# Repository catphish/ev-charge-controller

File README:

Charge Controller
=================

This controller has connectivity for CAN and EVSE as well as 4 x 12V digital inputs and 4 x low side switches.

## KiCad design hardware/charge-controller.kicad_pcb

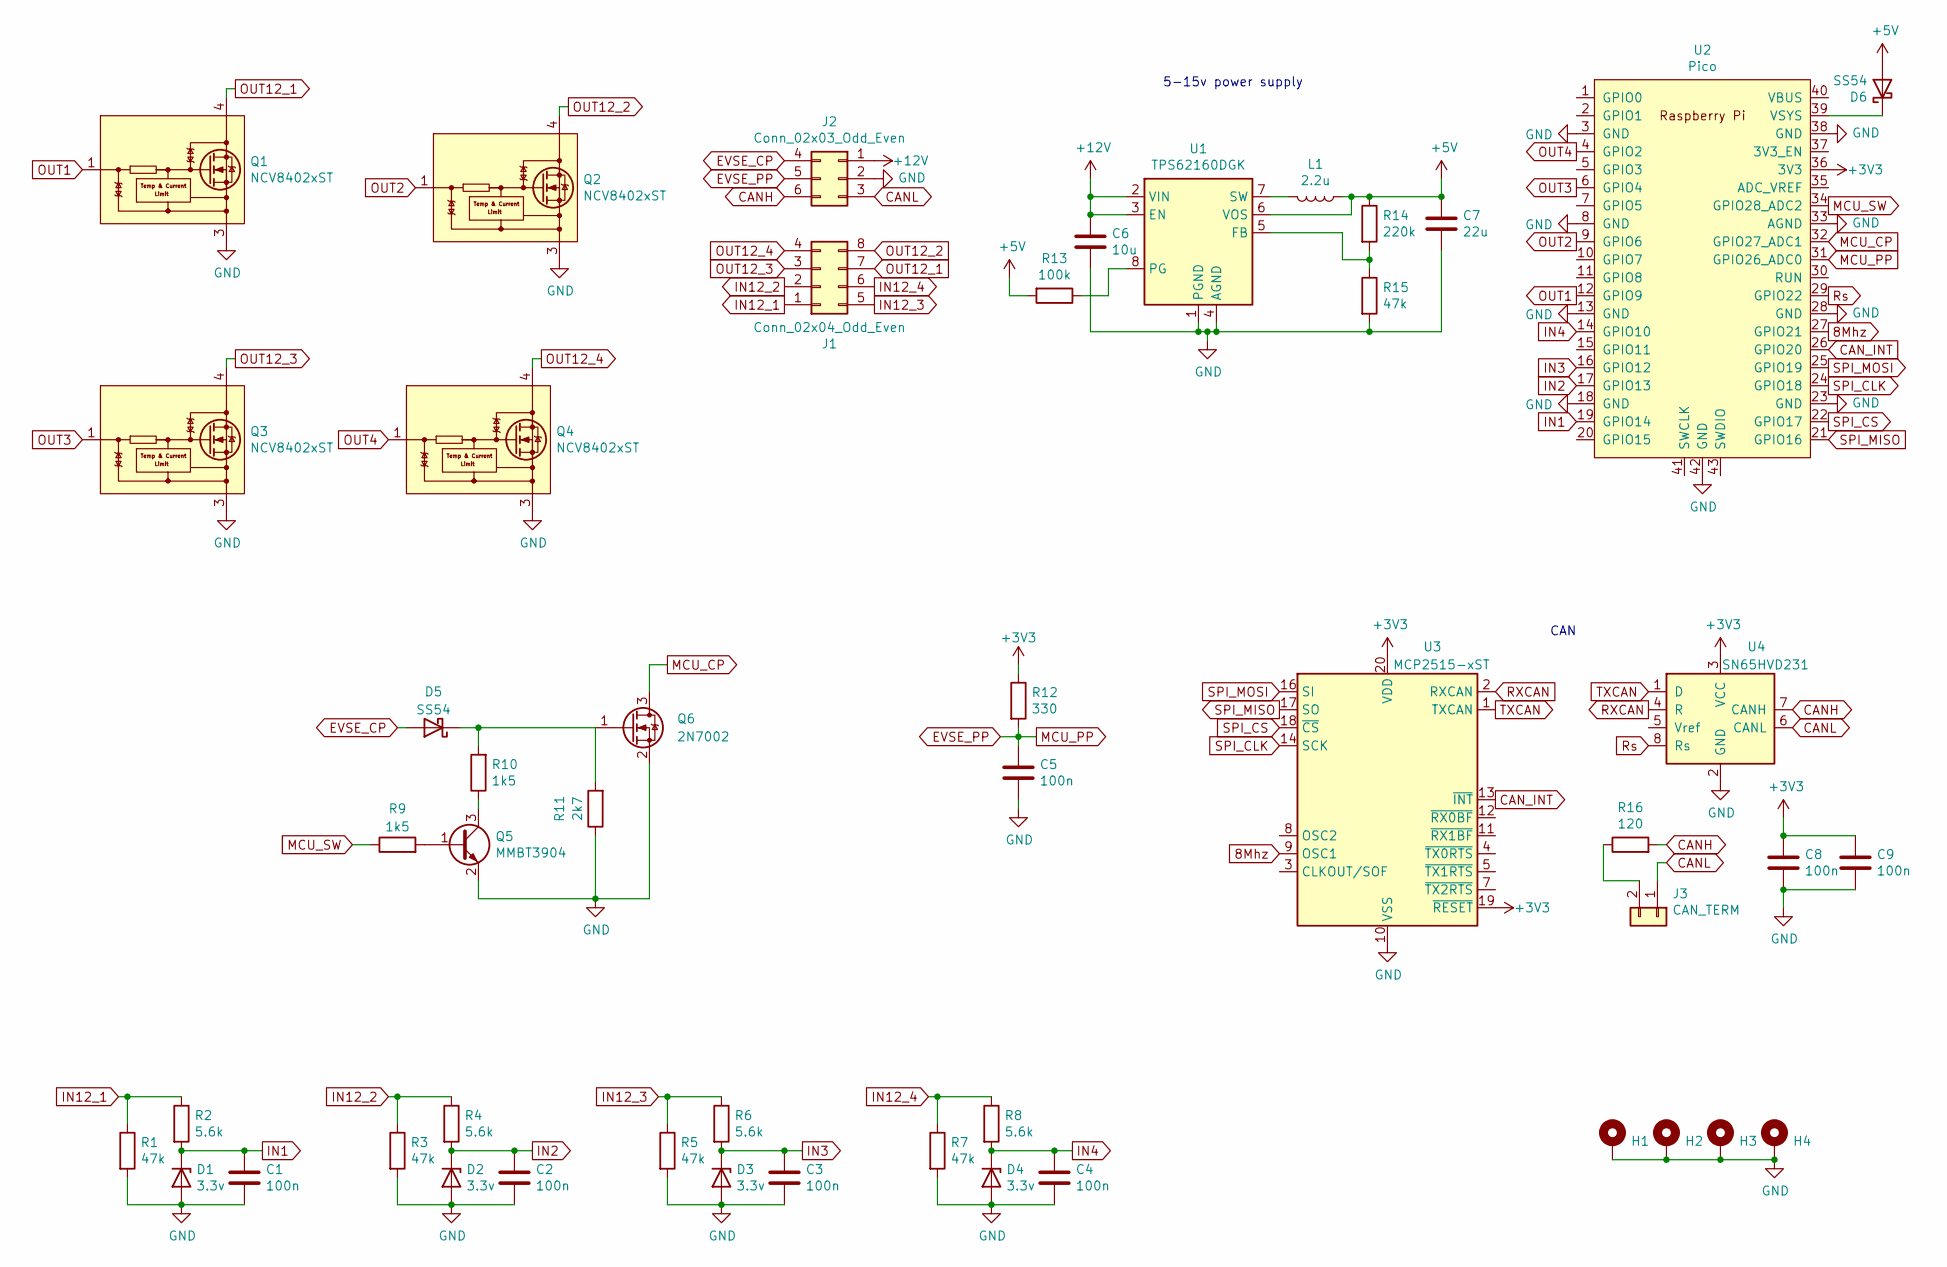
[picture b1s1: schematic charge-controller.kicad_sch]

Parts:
C1, C2, C3, C4, C5, C8, C9: 100n; C_0603_1608Metric; LCSC C14663
C6: 10u; C_1210_3225Metric; LCSC C77102
C7: 22u; C_1206_3216Metric; LCSC C5672
D1, D2, D3, D4: 3.3v; D_MiniMELF; LCSC C8056
D5, D6: SS54; D_SMA; LCSC C22452
H1, H2, H3, H4: MountingHole; MountingHole_3.2mm_M3_Pad
J1: Conn_02x04_Odd_Even; Molex_Micro-Fit_3.0_43045-0800_2x04_P3.00mm_Horizontal
J2: Conn_02x03_Odd_Even; Molex_Micro-Fit_3.0_43045-0600_2x03_P3.00mm_Horizontal
J3: CAN_TERM; PinHeader_1x02_P2.54mm_Vertical
L1: 2.2u; L_Neosid_SMS-ME3015; LCSC C43389
Q1, Q2, Q3, Q4: NCV8402xST; SOT-223; LCSC C77755
Q5: MMBT3904; SOT-23; LCSC C20526
Q6: 2N7002; SOT-23; LCSC C8545
R1, R3, R5, R7, R15: 47k; R_0603_1608Metric; LCSC C25819
R2, R4, R6, R8: 5.6k; R_0603_1608Metric; LCSC C23189
R9, R10: 1k5; R_0603_1608Metric; LCSC C22843
R11: 2k7; R_0603_1608Metric; LCSC C13167
R12: 330; R_0603_1608Metric; LCSC C23138
R13: 100k; R_0603_1608Metric; LCSC C25803
R14: 220k; R_0603_1608Metric; LCSC C22961
R16: 120; R_1206_3216Metric; LCSC C17909
U1: TPS62160DGK; MSOP-8_3x3mm_P0.65mm; LCSC C60726
U2: Pico; RPi_Pico_SMD_TH
U3: MCP2515-xST; TSSOP-20_4.4x6.5mm_P0.65mm; LCSC C15193
U4: SN65HVD231; SOIC-8_3.9x4.9mm_P1.27mm; LCSC C129257

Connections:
8Mhz: U2.27 (GPIO21), U3.9 (OSC1)
+3V3: C8.1, C9.1, R12.1, U2.36 (3V3), U3.19 (~RESET), U3.20 (VDD), U4.3 (VCC)
+5V: C7.1, D6.2 (A), L1.1, R13.2, R14.1, U1.6 (VOS)
+12V: C6.1, J2.1, U1.2 (VIN), U1.3 (EN)
CANH: J2.6, R16.2, U4.7 (CANH)
CANL: J2.3, J3.1, U4.6 (CANL)
CAN_INT: U2.26 (GPIO20), U3.13 (~INT)
EVSE_CP: D5.2 (A), J2.4
EVSE_PP: C5.1, J2.5, R12.2, U2.31 (GPIO26_ADC0)
GND: C1.2, C2.2, C3.2, C4.2, C5.2, C6.2, C7.2, C8.2, C9.2, D1.2 (A), D2.2 (A), D3.2 (A), D4.2 (A), H1.1, H2.1, H3.1, H4.1, J2.2, Q1.3 (S), Q2.3 (S), Q3.3 (S), Q4.3 (S), Q5.2 (E), Q6.2 (S), R1.2, R3.2, R5.2, R7.2, R11.1, R15.2, U1.1 (PGND), U1.4 (AGND), U2.3 (GND), U2.8 (GND), U2.13 (GND), U2.18 (GND), U2.23 (GND), U2.28 (GND), U2.33 (AGND), U2.38 (GND), U2.42 (GND), U3.10 (VSS), U4.2 (GND)
IN1: C1.1, D1.1 (K), R2.2, U2.19 (GPIO14)
IN2: C2.1, D2.1 (K), R4.2, U2.17 (GPIO13)
IN3: C3.1, D3.1 (K), R6.2, U2.16 (GPIO12)
IN4: C4.1, D4.1 (K), R8.2, U2.14 (GPIO10)
IN12_1: J1.1, R1.1, R2.1
IN12_2: J1.2, R3.1, R4.1
IN12_3: J1.5, R5.1, R6.1
IN12_4: J1.6, R7.1, R8.1
MCU_CP: Q6.3 (D), U2.32 (GPIO27_ADC1)
MCU_SW: R9.1, U2.34 (GPIO28_ADC2)
unnamed: D5.1 (K), Q6.1 (G), R10.2, R11.2
unnamed: D6.1 (K), U2.39 (VSYS)
unnamed: J3.2, R16.1
unnamed: L1.2, U1.7 (SW)
unnamed: Q5.1 (B), R9.2
unnamed: Q5.3 (C), R10.1
unnamed: R13.1, U1.8 (PG)
unnamed: R14.2, R15.1, U1.5 (FB)
OUT1: Q1.1 (G), U2.12 (GPIO9)
OUT2: Q2.1 (G), U2.9 (GPIO6)
OUT3: Q3.1 (G), U2.6 (GPIO4)
OUT4: Q4.1 (G), U2.4 (GPIO2)
OUT12_1: J1.7, Q1.2 (D), Q1.4 (D)
OUT12_2: J1.8, Q2.2 (D), Q2.4 (D)
OUT12_3: J1.3, Q3.2 (D), Q3.4 (D)
OUT12_4: J1.4, Q4.2 (D), Q4.4 (D)
RXCAN: U3.2 (RXCAN), U4.4 (R)
Rs: U2.29 (GPIO22), U4.8 (Rs)
SPI_CLK: U2.24 (GPIO18), U3.14 (SCK)
SPI_CS: U2.22 (GPIO17), U3.18 (~CS)
SPI_MISO: U2.21 (GPIO16), U3.17 (SO)
SPI_MOSI: U2.25 (GPIO19), U3.16 (SI)
TXCAN: U3.1 (TXCAN), U4.1 (D)

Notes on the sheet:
CAN
5-15v power supply

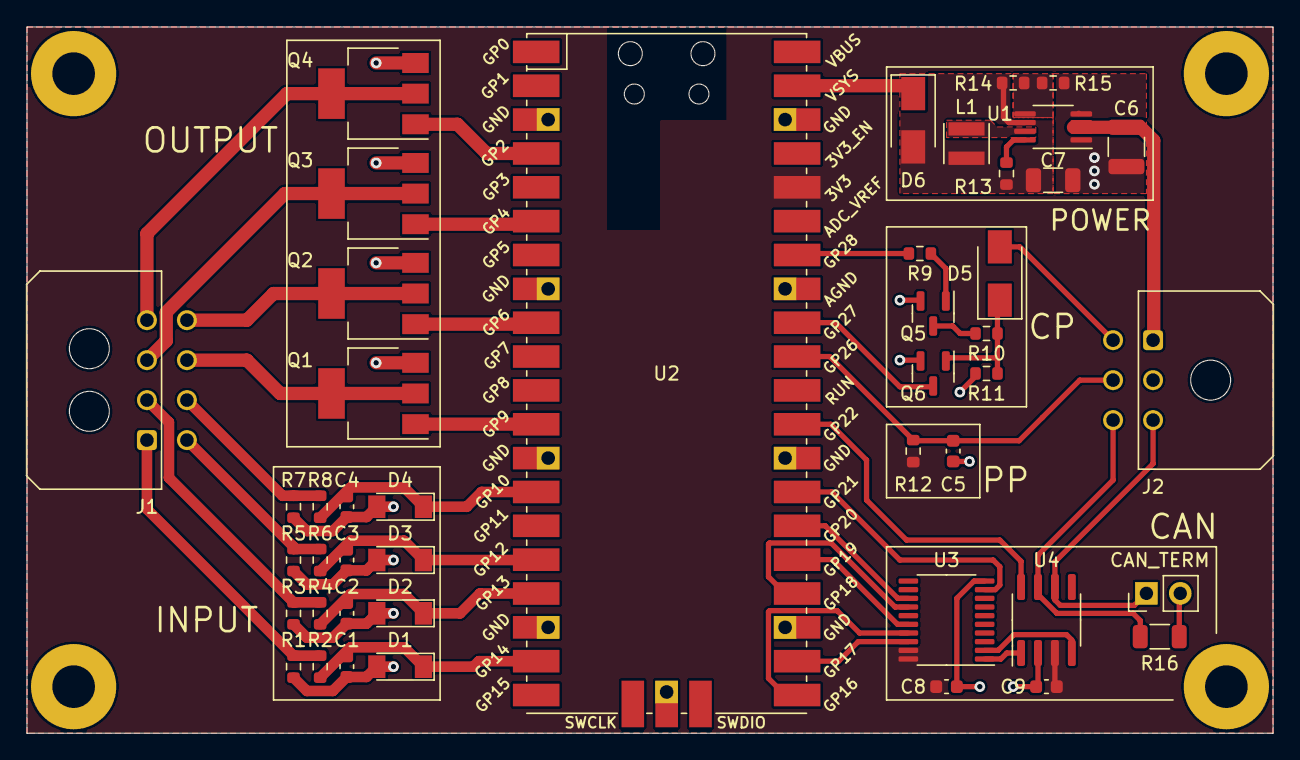
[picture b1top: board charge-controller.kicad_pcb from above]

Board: 2 copper layers, 93.5 x 53.0 mm, 49 parts (0 on the bottom side), 43 nets.

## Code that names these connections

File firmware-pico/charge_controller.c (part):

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
// Define pins for SPI (to CAN)
#define SPI_PORT spi0
#define SPI_MISO 16
#define SPI_CS 17
#define SPI_CLK 18
#define SPI_MOSI 19
#define CAN_INT 20
#define CAN_CLK 21  // 8MHz clock for CAN
#define CAN_SLEEP 22

// EVSE pins
#define EVSE_PP 26
#define EVSE_CP 27
#define EVSE_OUT 28

// GPIO pins
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#define IN2 13
#define IN3 12
#define IN4 10
#define OUT1 9
#define OUT2 6
#define OUT3 4
#define OUT4 2

#define IGNITION_IN IN3  // Detect ignition live
#define HEAT_IN IN4      // Input from heat switch
#define START_IN IN1     // Inut from start button

#define DC_DC_OUT OUT4  // Output to DC-DC converter enable relay
#define HEAT_OUT OUT2   // Output to heater relay

// State
int32_t pwm_value;
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void SPI_configure() {
  spi_init(SPI_PORT, 1000000);
  spi_set_format(SPI_PORT, 8, 0, 0, SPI_MSB_FIRST);
  gpio_set_function(SPI_MISO, GPIO_FUNC_SPI);
  gpio_set_function(SPI_MOSI, GPIO_FUNC_SPI);
  gpio_set_function(SPI_CLK, GPIO_FUNC_SPI);
  gpio_init(SPI_CS);
  gpio_set_dir(SPI_CS, GPIO_OUT);
  gpio_put(SPI_CS, 1);
}

void CAN_reset() {
  gpio_put(SPI_CS, 0);
  spi_write_blocking(SPI_PORT, (uint8_t[]){CMD_RESET}, 1);
  gpio_put(SPI_CS, 1);
  busy_wait_us(100);
}

uint8_t CAN_reg_read(uint8_t reg) {
  uint8_t data;
  gpio_put(SPI_CS, 0);
  spi_write_blocking(SPI_PORT, (uint8_t[]){CMD_READ, reg}, 2);
  spi_read_blocking(SPI_PORT, 0, &data, 1);
  gpio_put(SPI_CS, 1);
  return (data);
}

void CAN_reg_write(uint8_t reg, uint8_t val) {
  gpio_put(SPI_CS, 0);
  spi_write_blocking(SPI_PORT, (uint8_t[]){CMD_WRITE, reg, val}, 3);
  gpio_put(SPI_CS, 1);
}

void CAN_reg_modify(uint8_t reg, uint8_t mask, uint8_t val) {
  gpio_put(SPI_CS, 0);
  busy_wait_us(2);
  spi_write_blocking(SPI_PORT, (uint8_t[]){CMD_MODIFY, reg, mask, val}, 4);
  busy_wait_us(2);
  gpio_put(SPI_CS, 1);
}

void CAN_configure() {
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// Interrupt for CAN and dummy interrupt for hardware wakeup
void gpio_callback() {
  // CAN_receive();
  gpio_acknowledge_irq(CAN_INT, GPIO_IRQ_LEVEL_LOW);
}

void reconfigure_clocks() {
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  CAN_reg_write(REG_CANCTRL, MODE_SLEEP);
  gpio_put(CAN_SLEEP, 1);  // Sleep the CAN transceiver
  uint32_t s = save_and_disable_interrupts();
  gpio_set_irq_enabled_with_callback(EVSE_CP, GPIO_IRQ_LEVEL_LOW, true, &gpio_callback);
  gpio_set_irq_enabled_with_callback(IGNITION_IN, GPIO_IRQ_LEVEL_HIGH, true, &gpio_callback);
  gpio_set_dormant_irq_enabled(EVSE_CP, GPIO_IRQ_LEVEL_LOW, true);
  gpio_set_dormant_irq_enabled(IGNITION_IN, GPIO_IRQ_LEVEL_HIGH, true);
  clocks_hw->sleep_en0 = 0;
  clocks_hw->sleep_en1 = 0;
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  max_temp = 0;
  min_temp = 0;

  gpio_set_irq_enabled_with_callback(EVSE_CP, GPIO_IRQ_LEVEL_LOW, false, &gpio_callback);
  gpio_set_irq_enabled_with_callback(IGNITION_IN, GPIO_IRQ_LEVEL_HIGH, false, &gpio_callback);
  restore_interrupts(s);
  SPI_configure();
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  CAN_reset();
  CAN_configure();
  // Configure CAN interrupt input pin
  // gpio_init(CAN_INT);
  // gpio_set_dir(CAN_INT, GPIO_IN);
  // gpio_disable_pulls(CAN_INT);
  // gpio_set_irq_enabled_with_callback(CAN_INT, GPIO_IRQ_LEVEL_LOW, true, &gpio_callback);

  uint32_t dma_channel_1 = dma_claim_unused_channel(true);
  uint32_t dma_channel_2 = dma_claim_unused_channel(true);
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
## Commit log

2021-12-24 tidy up traces
2021-12-24 add logo
2022-01-08 add firmware boilerplate
2022-01-08 improve 12v inputs, connect CAN line driver sleep pin
2022-01-10 update schematic and picture
2022-01-12 rework inuts
2022-01-13 finish inputs
2022-01-30 begin EVSE comms
2022-01-30 simple code to activate contactor and battery warning lights
2022-04-01 temperature warning light, PWM fuel gauge
2022-05-10 open contactors when cells fully discharged
2022-05-20 major work on charging, EVSE comms, BMS comms
2022-05-21 low power sleep
2022-05-22 charger CAN output
2022-05-22 CAN fixes and improvements
2022-05-23 dc-dc converter control
2022-06-01 tidying, add under temperature protection, configure GPIO for Datsun test
2022-06-01 replace static USB mode with dynamic USB detection
2022-06-18 final jetski changes
2022-07-05 firmware formatting and VX220 specific additions
2022-07-14 low voltage cutoff for heater, stop charging at 4.0V
2022-08-03 remove interrupts, for reasons i can't be bothered to understand, sometimes they get stuck in a loop
2022-09-21 hardware fix for CP line
2022-12-23 code formatting
2022-12-28 simplify formatting, remove unused ignition handling code
2022-12-28 rmeove odd config line
2022-12-28 tidy formatting
2022-12-28 support for dual BMS
2022-12-28 make cell count a constant
2023-02-16 reduce charge temperature limit
2023-02-16 can stuff
2023-03-22 Remove interrupts and poll CAN
2023-03-22 update hardware from master branch wit CP/PP fixes
2023-03-22 Fix pin definition, ensure DCDC shutdown on sleep
2023-03-22 fix small register typo
2023-03-22 small formatting fix
2023-03-22 small formatting fixes
2023-03-22 remove unnecessayr line wraps
2023-03-22 minor formatting changes and comments
2023-03-22 more standardization with master, decrease min charge temp
2023-03-22 increase can timeout back to 10s
2023-10-03 Some changes to try to improve stability
2025-06-02 Add timer include which now seems to be required to use sleep
